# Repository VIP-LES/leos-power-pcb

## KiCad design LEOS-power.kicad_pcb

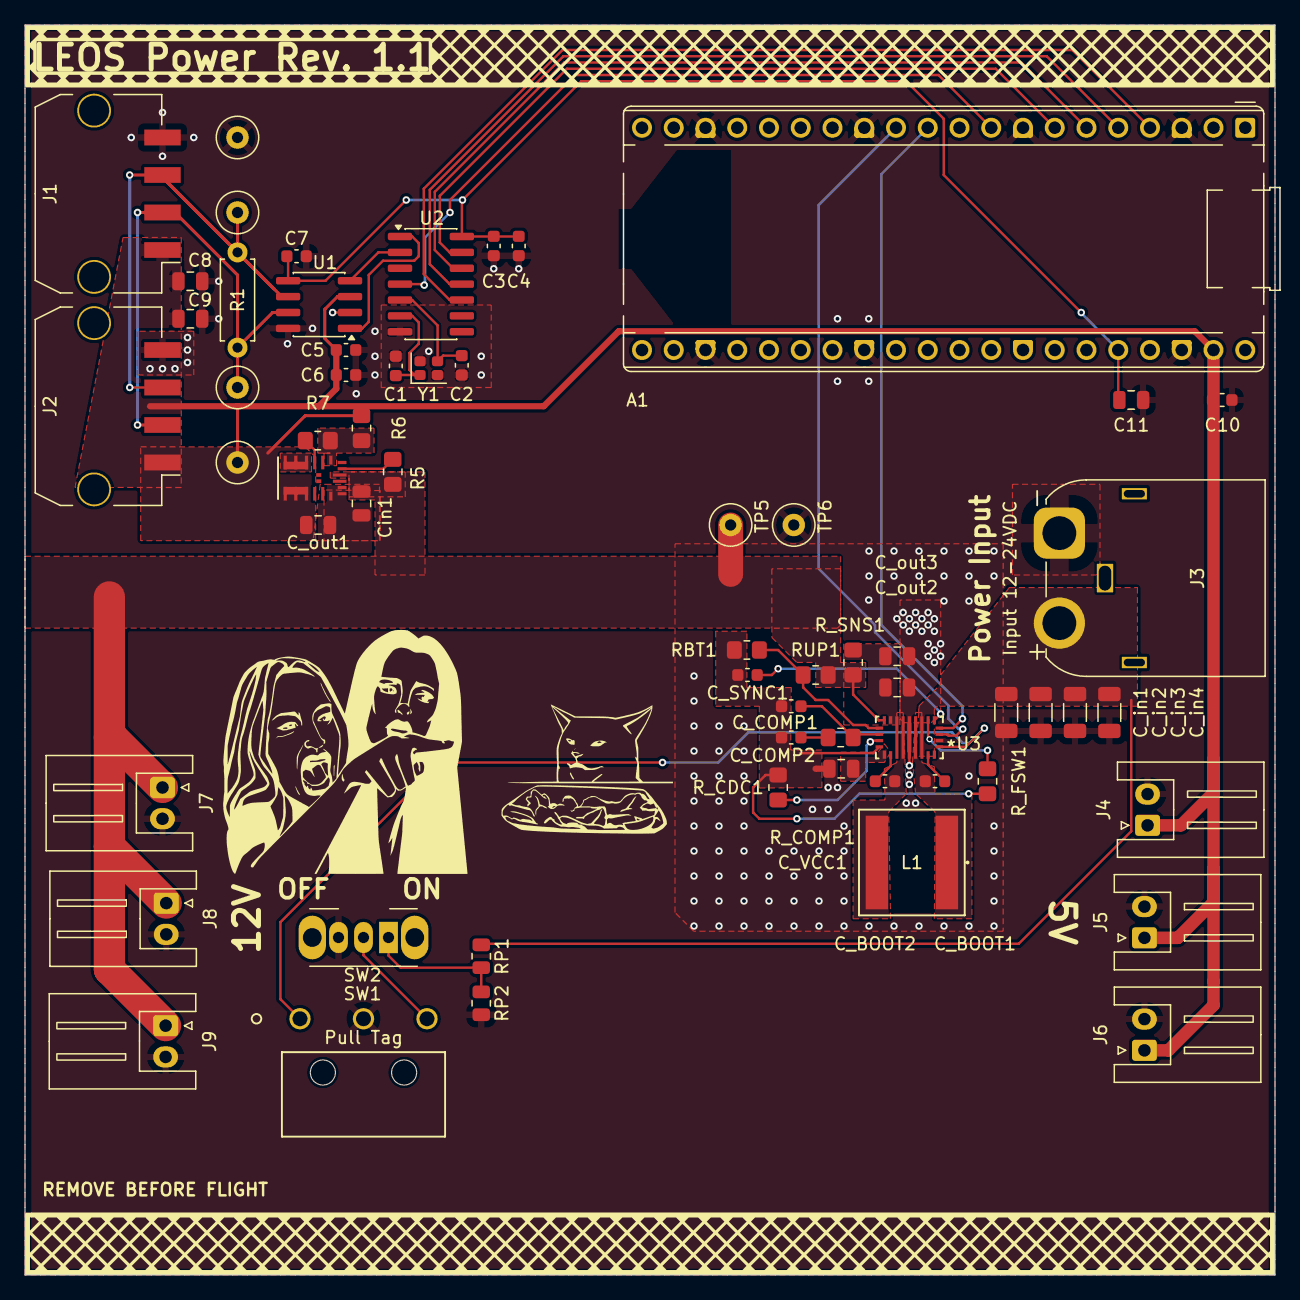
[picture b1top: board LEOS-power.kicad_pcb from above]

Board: 2 copper layers, 100.0 x 100.0 mm, 62 parts (0 on the bottom side), 38 nets.

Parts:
A1: RaspberryPi Pico; RaspberryPi_Pico_Common_THT
C1, C2: 10p; C_0603_1608Metric
C3, C5, C7, C10: 0.1u; C_0603_1608Metric
C4, C6: 1u; C_0603_1608Metric
C8, C9: 22u; C_0805_2012Metric
C11: 10u; C_0805_2012Metric
C_BOOT1, C_BOOT2: 0.1u; C_0603_1608Metric
C_COMP1: 33n; C_0603_1608Metric
C_COMP2: 15n; C_0603_1608Metric
C_SYNC1: 47n; C_0603_1608Metric
C_VCC1: 4.7u; C_0805_2012Metric
C_in1, C_in2, C_in3, C_in4: 10u; C_1206_3216Metric
C_out1, C_out2, C_out3: 22u; C_0805_2012Metric
Cin1: 10u; C_0805_2012Metric
J1, J2: MicroFit_1x4; Molex_MicroFit3.0_43650-0410_1x04_Horizontal
J3: Power Input; AMASS_XT60IPW-M_1x03_P7.20mm_Horizontal
J4, J5, J6: 5V; JST_XH_S2B-XH-A_1x02_P2.50mm_Horizontal
J7, J8, J9: 12V; JST_XH_S2B-XH-A_1x02_P2.50mm_Horizontal
L1: 10u; IND_TAIYO_NRS8030_TAY
NT1: NetTie_2; NetTie-2_SMD_Pad0.5mm
R1: 120; R_Axial_DIN0207_L6.3mm_D2.5mm_P7.62mm_Horizontal
R5, R6: 100k; R_0805_2012Metric_Pad1.20x1.40mm_HandSolder
R7: 19.1k; R_0805_2012Metric_Pad1.20x1.40mm_HandSolder
RBT1: 11k; R_0805_2012Metric_Pad1.20x1.40mm_HandSolder
RP1: 750k; R_0805_2012Metric
RP2: 100k; R_0805_2012Metric
RUP1: 100k; R_0805_2012Metric_Pad1.20x1.40mm_HandSolder
R_CDC1: 20k; R_0805_2012Metric_Pad1.20x1.40mm_HandSolder
R_COMP1: 7.5k; R_0805_2012Metric_Pad1.20x1.40mm_HandSolder
R_FSW1: 9.1k; R_0805_2012Metric_Pad1.20x1.40mm_HandSolder
R_SNS1: 16m; R_0805_2012Metric_Pad1.20x1.40mm_HandSolder
SW1: Pull Tag; D2F-FL-A1
SW2: Power Switch; SW_Slide_SPDT_Angled_CK_OS102011MA1Q
TP1: CAN-H Test Point; TestPoint_Loop_D2.60mm_Drill0.9mm_Beaded
TP2: CAN-L Test Point; TestPoint_Loop_D2.60mm_Drill0.9mm_Beaded
TP3: 5V Test Point; TestPoint_Loop_D2.60mm_Drill0.9mm_Beaded
TP4, TP6: GND Test Point; TestPoint_Loop_D2.60mm_Drill0.9mm_Beaded
TP5: 12V Test; TestPoint_Loop_D2.60mm_Drill0.9mm_Beaded
U1: MCP2562FD; SOIC-8_3.9x4.9mm_P1.27mm
U2: MCP2518FD; SOIC-14_3.9x8.7mm_P1.27mm
U3: TPS55287; VQFN21_RYQ_TEX
U4: MPM3620A; IC18_MPM3620AGQV-Z_MNP
Y1: 40 MHz; Crystal_SMD_2016-4Pin_2.0x1.6mm

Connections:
+5V: A1.39 (VSYS), C5.1, C6.1, C8.1, C9.1, C10.1, C_out1.1, J1.1, J2.1, J4.1, J5.1, J6.1, R6.1, TP3.1, U1.3 (VDD), U4.7 (OUT), U4.8 (OUT), U4.9 (OUT), U4.22 (OUT)
+12V: Cin1.1, J7.1, J8.1, J9.1, R5.1, RUP1.2, R_SNS1.2, TP5.1, U3.13 (ISN), U4.16 (IN)
/CANbus/CAN+: J1.2, J2.2, R1.2, TP1.1, U1.7 (CANH)
/CANbus/CAN-: J1.3, J2.3, R1.1, TP2.1, U1.6 (CANL)
/CANbus/CS: A1.7 (GPIO5), U2.13 (nCS)
/CANbus/INT: A1.9 (GPIO6), U2.4 (INT)
/CANbus/MISO: A1.6 (GPIO4), U2.12 (SDO)
/CANbus/MOSI: A1.5 (GPIO3), U2.11 (SDI)
/CANbus/OSC1: C1.2, U2.6 (OSC1), Y1.1
/CANbus/OSC2: C2.2, U2.5 (OSC2), Y1.3
/CANbus/SCK: A1.4 (GPIO2), U2.10 (SCK)
/Power/EN: SW1.1 (A), U3.1 (EN/UVLO)
/Power/FB: R6.2, R7.1, U4.1 (FB)
/Power/SCL: A1.12 (GPIO9), U3.3 (SCL)
/Power/SDA: A1.11 (GPIO8), U3.4 (SDA)
/Power/SW: U4.4 (SW), U4.5 (SW), U4.6 (SW), U4.21 (SW)
GND: A1.3 (GND), A1.8 (GND), A1.13 (GND), A1.18 (GND), A1.23 (GND), A1.28 (GND), A1.38 (GND), C1.1, C2.1, C3.2, C4.2, C5.2, C6.2, C7.2, C8.2, C9.2, C10.2, C11.2, C_VCC1.2, C_in1.2, C_in2.2, C_in3.2, C_in4.2, C_out1.2, C_out2.1, C_out3.1, Cin1.2, J1.4, J2.4, J3.1, J4.2, J5.2, J6.2, J7.2, J8.2, J9.2, NT1.2, RP2.2, SW1.2 (B), SW2.3 (C), TP4.1, TP6.1, U1.2 (VSS), U1.8 (STBY), U2.7 (VSS), U3.2 (MODE), U3.9 (PGND), U4.12 (PGND), U4.13 (PGND), U4.14 (PGND), Y1.2 (G), Y1.4 (G)
GNDA: C_COMP1.2, C_COMP2.2, C_SYNC1.2, NT1.1, RBT1.1, R_CDC1.2, R_FSW1.2, U3.17 (AGND)
GNDA2: R7.2, U4.3 (AGND)
unnamed: C_COMP2.1, R_COMP1.2
unnamed: SW1.3 (C), SW2.2 (B)
unnamed: RP1.2, RP2.1, SW2.1 (A)
unnamed: U1.4 (RXD), U2.2 (RXCAN)
unnamed: U1.1 (TXD), U2.1 (TXCAN)
unnamed: C_BOOT1.2, U3.20 (BOOT1)
unnamed: C_BOOT2.2, U3.19 (BOOT2)
unnamed: R_CDC1.1, U3.16 (CDC)
unnamed: C_COMP1.1, R_COMP1.1, U3.15 (COMP)
unnamed: C_SYNC1.1, U3.5 (DITH/SYNC)
unnamed: RBT1.2, RUP1.1, U3.14 (FB/INT)
unnamed: R_FSW1.1, U3.6 (FSW)
unnamed: C_out2.2, C_out3.2, R_SNS1.1, U3.11 (VOUT), U3.12 (ISP)
unnamed: C_BOOT1.1, L1.1, U3.8 (SW1)
unnamed: C_BOOT2.1, L1.2, U3.10 (SW2)
unnamed: C_VCC1.1, U3.18 (VCC)
unnamed: R5.2, U4.17 (EN)
VDC: C_in1.1, C_in2.1, C_in3.1, C_in4.1, J3.2, RP1.1, U3.7 (VIN)
VDD: A1.36 (3V3), C3.1, C4.1, C7.1, C11.1, U1.5 (VIO), U2.14 (VDD)

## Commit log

2026-02-06 Added buck converter and components, plus their values
2026-02-06 Added the 12-5V buck converter to the schematic
2026-02-06 added a 12-5V buck converter to the schematic
2026-02-11 updates to schematic and added footprints
2026-02-13 routed the 12-5V buck converter
2026-02-14 mostly routed the vin to 12V buck converter
2026-02-18 added some more ground nodes
2026-02-18 added more ground nodes
2026-02-18 connected the Vin to 12V buck converter to ground!!!!!!
2026-02-20 Update to new template
2026-02-20 add .gitignore
2026-02-20 Power board complete v1.0
2026-02-20 v1.1 Fix UVLO and EN power source
2026-04-23 Add files via upload
    battery to 12V buck converter documentation
2026-04-23 Docuemntnsaigton

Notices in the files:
parts and their libraries:
Copyright 2016 Accelerated Designs. All rights reserved.
